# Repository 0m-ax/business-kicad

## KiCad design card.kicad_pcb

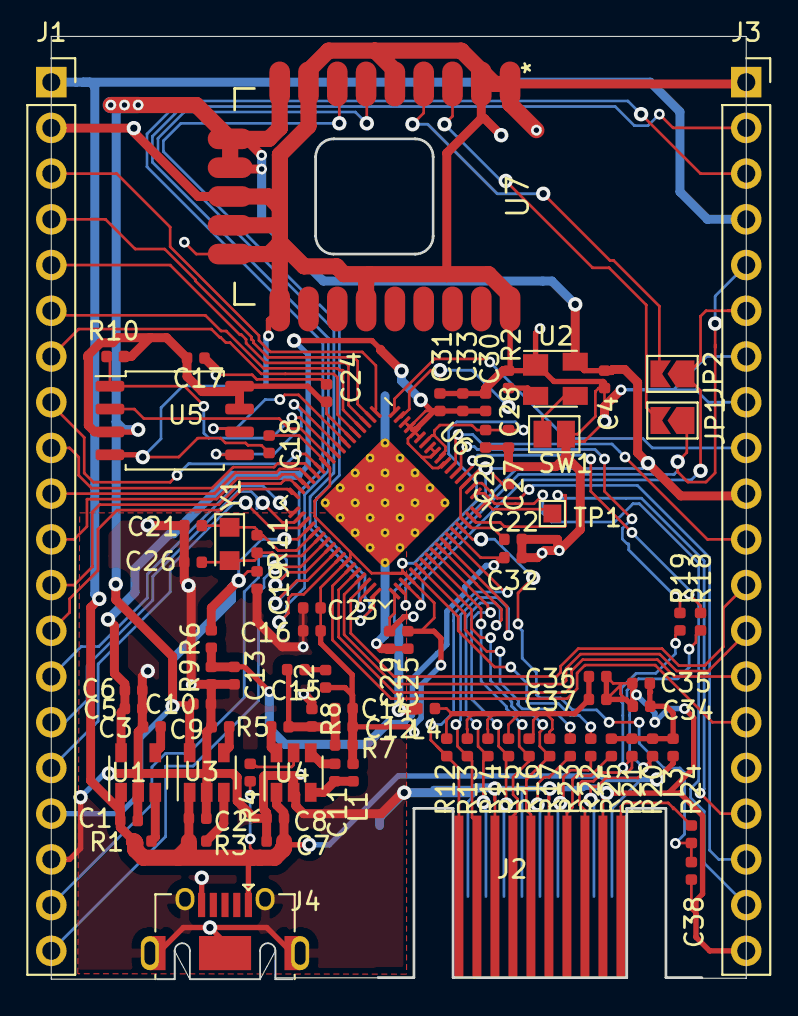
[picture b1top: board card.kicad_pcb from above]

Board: 2 copper layers, 38.5 x 52.3 mm, 83 parts (0 on the bottom side), 77 nets.

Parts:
C1, C4, C5, C8, C14, C17, C32, C35, C36, C37, C38: 100nF; C_0402_1005Metric
C2: C; C_0402_1005Metric
C3, C9, C10: 10nF; C_0402_1005Metric
C6, C13, C16, C18, C19, C20, C22, C23, C24, C25, C27, C28, C29, C30, C31, C33, C34: 10uF; C_0402_1005Metric
C7, C12, C15: 22uF; C_0402_1005Metric
C11: 1uF; C_0402_1005Metric
C21, C26: 20pF; C_0402_1005Metric
J1, J3: Conn_01x20_Male; PinSocket_1x20_P2.54mm_Vertical
J2: HDMI_A; HDMI-PCB
J4: USB_B_Micro; USB_Micro-AB_Molex_47590-0001
JP1, JP2: Jumper; SolderJumper-2_P1.3mm_Open_TrianglePad1.0x1.5mm
L1: 3.3uH; L_0402_1005Metric
L2, L4: 100r; L_0402_1005Metric
L3: L; L_0402_1005Metric
R1, R2, R4, R5: 100K; R_0402_1005Metric
R3: 100k; R_0402_1005Metric
R6, R18, R19, R22, R23: 33R; R_0402_1005Metric
R7: 20K; R_0402_1005Metric
R8: 47K; R_0402_1005Metric
R9: 1K; R_0402_1005Metric
R10: 4.7K; R_0402_1005Metric
R11: 1M; R_0402_1005Metric
R12, R13, R14, R16, R17: 100R; R_0402_1005Metric
R15: 100r; R_0402_1005Metric
R20, R21: 4.7k; R_0402_1005Metric
R24, R25: 10k; R_0402_1005Metric
SW1: SW_DPST_x2; SolderJumper-2_P1.3mm_Open_Pad1.0x1.5mm
TP1: TestPoint; TestPoint_Pad_1.0x1.0mm
U1: SPX3819-1.8; SOT-23-5
U2: IMP811REUS-T; SOT-143
U3: SP6205EM5-L-3-3_TR; SOT-23-5
U4: MP1469GJ; SOT-23-6
U5: W25Q32JVSS; SOIC-8_5.23x5.23mm_P1.27mm
U6: GX6605S; QFN-68-1EP_8x8mm_P0.4mm_EP5.2x5.2mm_ThermalVias
U7: BLUE-BEAN; BLUE-BEAN-A
Y1: 27MHz; Crystal_SMD_2012-2Pin_2.0x1.2mm_HandSoldering

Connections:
+1V0: C15.1, L2.2
+1V1: C12.1, C14.1, C16.1, C18.1, C20.1, C23.1, C25.1, C28.1, L1.2, L2.1, R7.2, U6.11, U6.28, U6.38, U6.59, U6.62
+1V8: C5.1, C6.1, C30.1, C31.1, C33.1, U1.5, U6.58, U6.60, U6.61, U6.63, U6.64, U6.65, U6.66
+2V5: C13.1, C32.1, R6.1, R9.1, U6.47
+3V3: C4.2, C10.1, C17.1, C19.1, C22.1, C24.1, C27.1, C29.1, J1.17, J3.10, L4.2, R6.2, R10.1, U2.4, U3.5, U5.3, U5.7, U5.8, U6.6, U6.21, U6.35, U6.49, U6.54, U7.9, U7.10, U7.11
+5C: C34.1, C35.1, L3.2, R20.2, R21.2, R25.2
+5V: C1.1, C2.1, C7.1, C8.1, J1.1, J2.18, J3.4, J4.1, L3.1, R1.2, R3.2, R4.2, U1.1, U3.1, U4.1
/CPU/SPI_CLK: U5.6, U6.7
/CPU/SPI_CSN: R10.2, U5.1, U6.9
/CPU/SPI_MISO: U5.2, U6.10
/CPU/SPI_MOSI: U5.5, U6.8
/CPU/X27M_6605_IN: C21.1, R11.2, U6.22, Y1.1
/CPU/X27M_6605_OUT: C26.1, R11.1, U6.23, Y1.2
ADCINNI: J3.12, U6.32
ADCINNQ: J3.15, U6.29
ADCINPI: J3.13, U6.31
ADCINPQ: J3.14, U6.30
AOL: J3.19, U6.52
AOR: J3.18, U6.53
GND: C1.2, C2.2, C3.2, C4.1, C5.2, C6.2, C7.2, C8.2, C9.2, C10.2, C13.2, C16.2, C17.2, C18.2, C19.2, C20.2, C21.2, C22.2, C23.2, C24.2, C25.2, C26.2, C27.2, C28.2, C29.2, C30.2, C31.2, C32.2, C33.2, C34.2, C35.2, C36.2, C37.2, C38.2, J1.2, J1.18, J2.2, J2.5, J2.8, J2.11, J2.17, J3.1, J3.7, J3.8, J3.20, J4.5, J4.6, R2.2, R8.1, R9.2, SW1.1, U1.2, U2.1, U3.2, U4.2, U5.4, U6.69, U7.1, U7.2, U7.5, U7.8, U7.12, U7.13, U7.14, U7.15, U7.18, U7.23
HDMI_PLG: C38.1, R24.2, U6.48
HDMI_SCL: R19.1, U6.56
HDMI_SDA: R18.1, U6.55
HOST0_DM: U6.34, U7.7
HOST0_DP: U6.33, U7.6
HOST1_DM: J3.6, JP2.1, U6.37
HOST1_DP: J3.5, JP1.1, U6.36
IR: J3.9, U6.68
MR: SW1.2, U2.3
NRST_GX_CPU: R2.1, U2.2, U6.67
unnamed: C3.1, U1.4
unnamed: C9.1, U3.4
unnamed: C11.1, L1.1, U4.3
unnamed: C11.2, U4.4
unnamed: C12.2, C14.2, C15.2, R5.1, R7.1, R8.2
unnamed: C36.1, C37.1, L4.1, R12.1, R13.1, R14.1, R15.1, R16.1, R17.1
unnamed: J2.10, R23.1
unnamed: J2.12, R22.1
unnamed: J2.13, R25.1
unnamed: J2.15, R19.2, R21.1
unnamed: J2.16, R18.2, R20.1
unnamed: J2.19, R24.1
unnamed: JP1.2, U7.3
unnamed: JP2.2, U7.4
unnamed: R1.1, U1.3
unnamed: R3.1, U3.3
unnamed: R4.1, U4.5
unnamed: R5.2, U4.6
unnamed: TP1.1, U6.51
PORT0: J1.3, U6.1
PORT1: J1.4, U6.2
PORT2: J1.5, U6.3
PORT3: J1.6, U6.4
PORT4: J1.7, U6.5
PORT5: J1.8, U6.12
PORT6: J1.9, U6.13
PORT7: J1.10, U6.14
PORT8: J1.11, U6.15
PORT9: J1.12, U6.16
PORT20: J3.11, U6.57
TX0_N: J2.9, R17.2, U6.41
TX0_P: J2.7, R16.2, U6.42
TX1_N: J2.6, R15.2, U6.43
TX1_P: J2.4, R14.2, U6.44
TX2_N: J2.3, R13.2, U6.45
TX2_P: J2.1, R12.2, U6.46
TXC_N: R22.2, U6.39
TXC_P: R23.2, U6.40
UART1-Rx: J3.2, U6.27
UART1-Tx: J3.3, U6.26
VOUT1: J3.17, U6.50
port10: J1.13, U6.17
port11: J1.14, U6.18
port12: J1.15, U6.19
port13: J1.16, U6.20
port14-SCL: J1.19, U6.25
port15-SDA: J1.20, U6.24

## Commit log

2020-08-29 inital commit
2020-08-29 added inital files
2020-08-29 added power
2020-08-29 added more PowerSuply stuffs
2020-08-29 added sybmols for power stuff, and finished circuit
2020-08-29 added sheeT for CPU
2020-08-29 added csky
2020-08-29 added CPU to CPU sheeT
2020-08-29 added power to CPU
2020-09-02 wired SPI flash to cpu, and added CPU lables
2020-09-03 added port / GPIO sheet to scimatic
2020-09-03 broke, out all GPIO and finsihed wiring HDMI
2020-09-03 added todo list before i feel aleeped on my keybard*
2020-09-05 finished scimatic for now, and started populating PCB. *chugs rrum*
2020-09-05 started layout of the PCB, allso moved onto craken rum, from captin morgan. please for the love of god check the footprints are right. @MAX
2020-09-05 added a 3d footprint for the Blue Bean. and were out of rum now, i drank most of the rum, i would ask why is the rum gone, but thats allready an old meme. ive not done much on this commit to be totat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
2020-09-08 started routing the PCB
2020-09-10 started some routing, removed some useless components
2020-09-11 added power allé, and did more routing
2020-09-21 did more routing
2020-09-21 removed USB power protection. did more routing
2020-09-22 started to add the HDMI port in the pcb
2020-09-23 finished the specal hdmi connector pcb, and looked aimliystly at usb micro
2021-04-13 did some routing and fixed some pinouts on components
2021-04-14 did some work on routing
2021-04-14 added solder jumpers for optonla blue tooth
2021-04-14 did a little bit more routing
2021-04-17 did some more routing
2021-04-22 did more routing! allmost done now!
2021-04-23 finished routing, and started neatnening up some of the ugly traces and silk screen
